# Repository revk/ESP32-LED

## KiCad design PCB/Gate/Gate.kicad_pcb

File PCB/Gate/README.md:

# Gate

## Trademark

This is an open source project, but bear in mind you cannot sell boards or cases bearing the Andrews & Arnold Ltd name, the A&A logo, the registered trademark AJK logo, or the GS1 allocated EANs assigned to Andrews & Arnold Ltd.

## PCB Designs

These files are for use with [KiCAD](https://www.kicad.org).

- [Gate](Gate.kicad_pro)

## 3D

3D case designs are normally automatically created from the PCB so as to ensure correct details and placement of apertures, etc.

- [Stargate](Stargate.stl)
- [StargateBottom](StargateBottom.stl)
- [StargateRamp](StargateRamp.stl)
- [StargateRampBottom](StargateRampBottom.stl)
- [StargateRampTop](StargateRampTop.stl)
- [StargateTop](StargateTop.stl)

## PCB Images

---

*Auto generated README.md 2025-11-09T11:03:06*

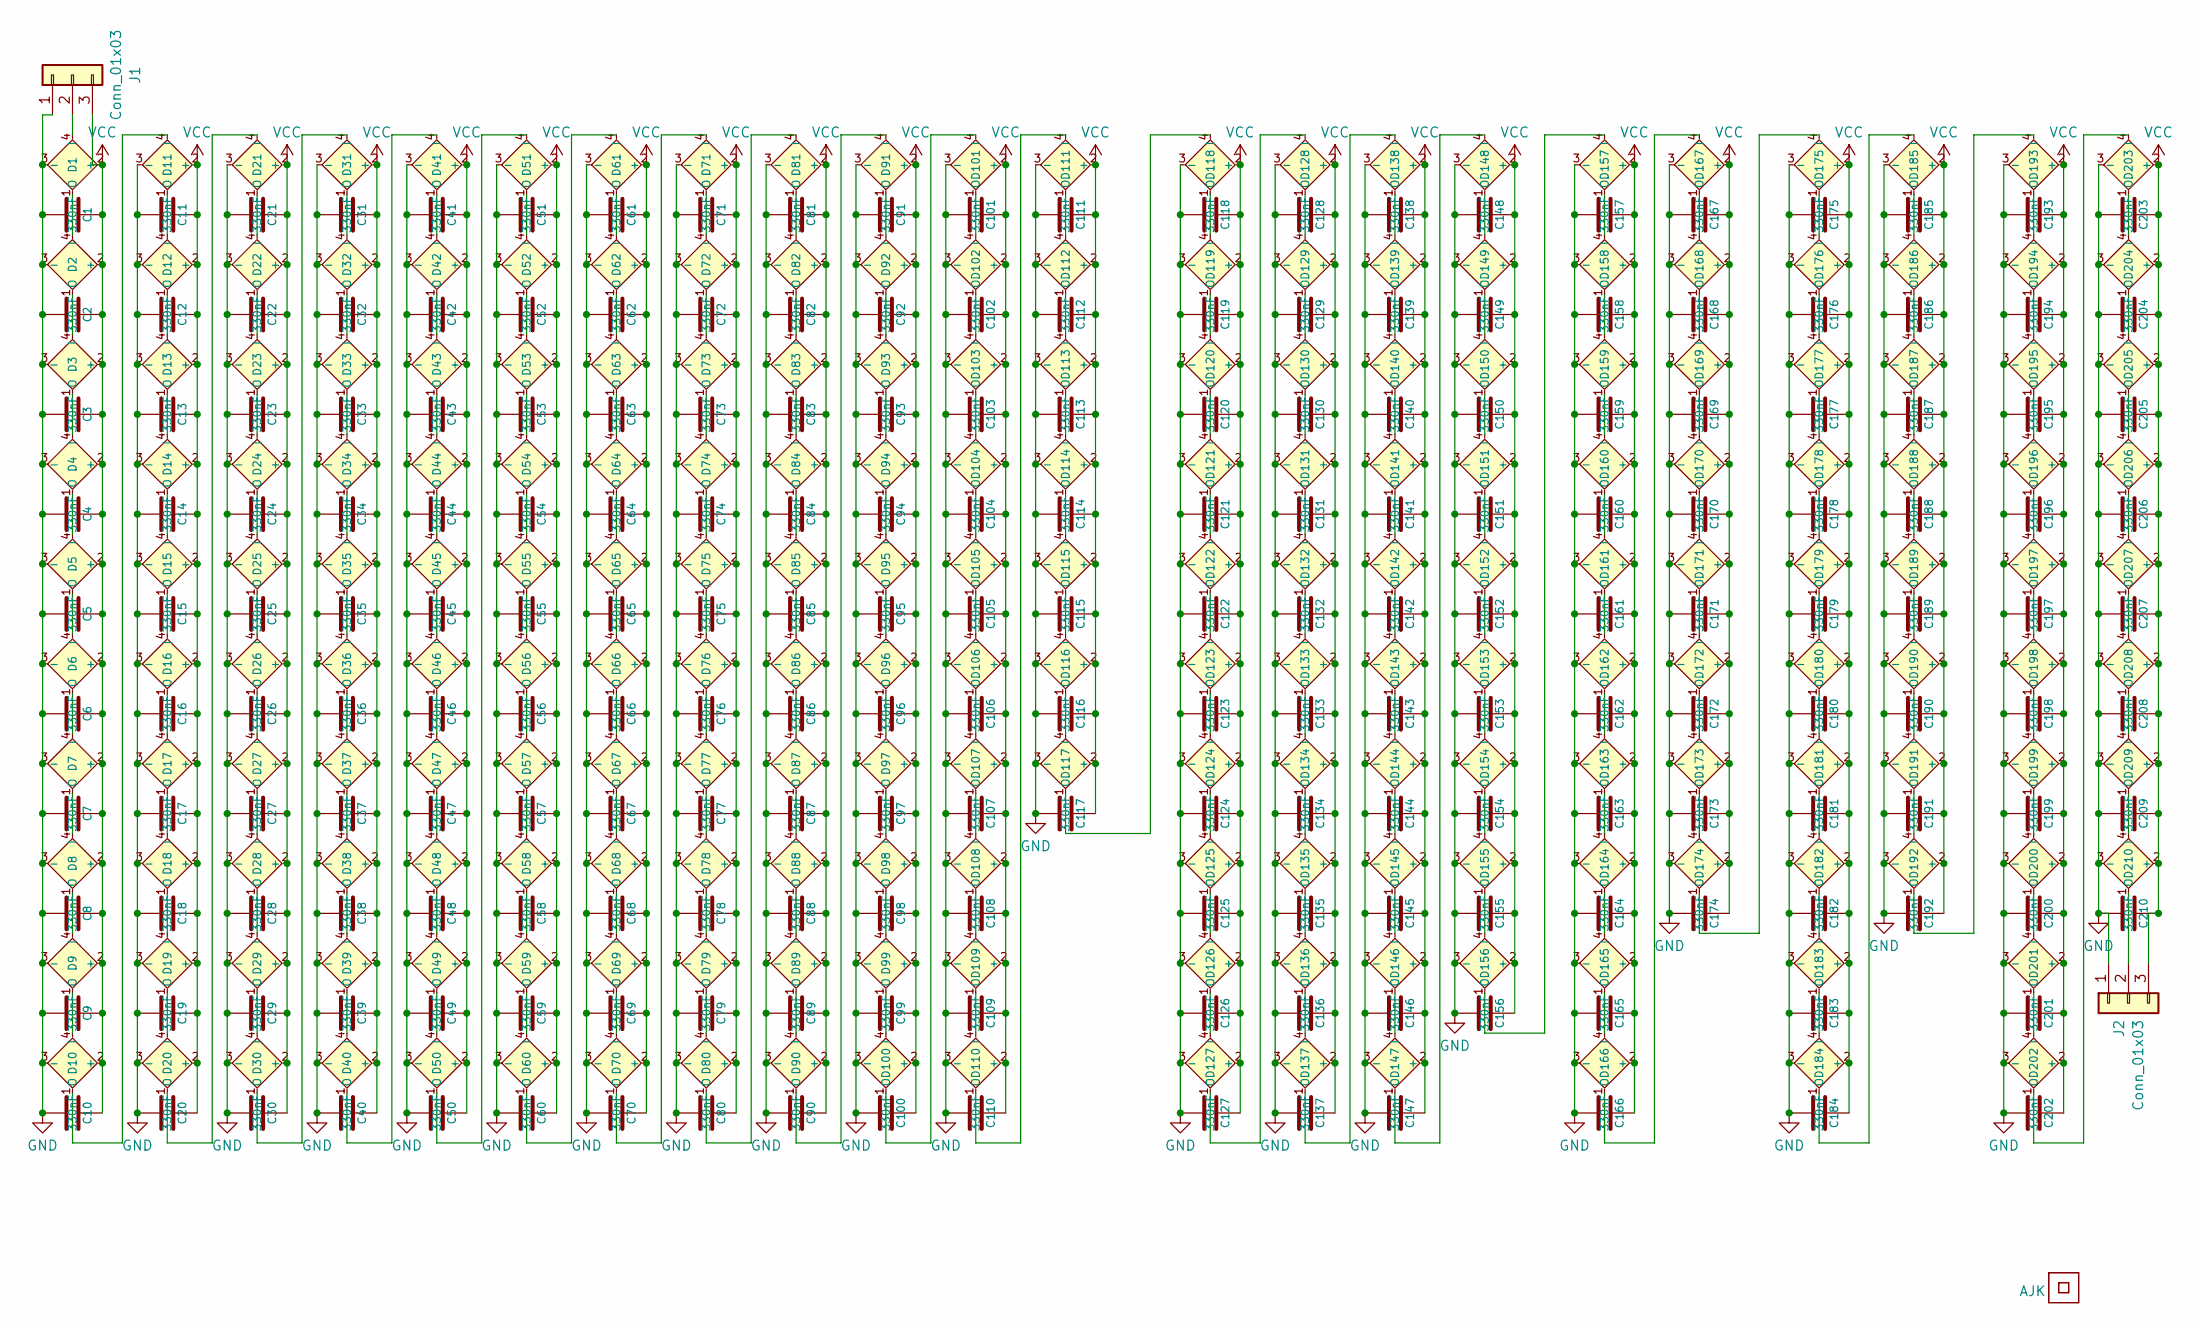
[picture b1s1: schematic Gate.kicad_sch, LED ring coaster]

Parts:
C1, C2, C3, C4, C5, C6, C7, C8, C9, C10, C11, C12, C13, C14, C15, C16, C17, C18, C19, C20, C21, C22, C23, C24, C25, C26, C27, C28, C29, C30, C31, C32, C33, C34, C35, C36, C37, C38, C39, C40, C41, C42, C43, C44, C45, C46, C47, C48, C49, C50, C51, C52, C53, C54, C55, C56, C57, C58, C59, C60, C61, C62, C63, C64, C65, C66, C67, C68, C69, C70, C71, C72, C73, C74, C75, C76, C77, C78, C79, C80, C81, C82, C83, C84, C85, C86, C87, C88, C89, C90, C91, C92, C93, C94, C95, C96, C97, C98, C99, C100, C101, C102, C103, C104, C105, C106, C107, C108, C109, C110, C111, C112, C113, C114, C115, C116, C117, C118, C119, C120, C121, C122, C123, C124, C125, C126, C127, C128, C129, C130, C131, C132, C133, C134, C135, C136, C137, C138, C139, C140, C141, C142, C143, C144, C145, C146, C147, C148, C149, C150, C151, C152, C153, C154, C155, C156, C157, C158, C159, C160, C161, C162, C163, C164, C165, C166, C167, C168, C169, C170, C171, C172, C173, C174, C175, C176, C177, C178, C179, C180, C181, C182, C183, C184, C185, C186, C187, C188, C189, C190, C191, C192, C193, C194, C195, C196, C197, C198, C199, C200, C201, C202, C203, C204, C205, C206, C207, C208, C209, C210: 330nF; C_0402
D1, D2, D3, D4, D5, D6, D7, D8, D9, D10, D11, D12, D13, D14, D15, D16, D17, D18, D19, D20, D21, D22, D23, D24, D25, D26, D27, D28, D29, D30, D31, D32, D33, D34, D35, D36, D37, D38, D39, D40, D41, D42, D43, D44, D45, D46, D47, D48, D49, D50, D51, D52, D53, D54, D55, D56, D57, D58, D59, D60, D61, D62, D63, D64, D65, D66, D67, D68, D69, D70, D71, D72, D73, D74, D75, D76, D77, D78, D79, D80, D81, D82, D83, D84, D85, D86, D87, D88, D89, D90, D91, D92, D93, D94, D95, D96, D97, D98, D99, D100, D101, D102, D103, D104, D105, D106, D107, D108, D109, D110, D111, D112, D113, D114, D115, D116, D117, D118, D119, D120, D121, D122, D123, D124, D125, D126, D127, D128, D129, D130, D131, D132, D133, D134, D135, D136, D137, D138, D139, D140, D141, D142, D143, D144, D145, D146, D147, D148, D149, D150, D151, D152, D153, D154, D155, D156, D157, D158, D159, D160, D161, D162, D163, D164, D165, D166, D167, D168, D169, D170, D171, D172, D173, D174, D175, D176, D177, D178, D179, D180, D181, D182, D183, D184, D185, D186, D187, D188, D189, D190, D191, D192, D193, D194, D195, D196, D197, D198, D199, D200, D201, D202, D203, D204, D205, D206, D207, D208, D209, D210: XL-1010RGBC-WS2812B; SMD1010; LCSC Part # C5349953
J1, J2: Conn_01x03; 3-PADS
Logo1: AJK
U1: QR; QR-LED

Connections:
GND: C1.2, C2.2, C3.2, C4.2, C5.2, C6.2, C7.2, C8.2, C9.2, C10.2, C11.2, C12.2, C13.2, C14.2, C15.2, C16.2, C17.2, C18.2, C19.2, C20.2, C21.2, C22.2, C23.2, C24.2, C25.2, C26.2, C27.2, C28.2, C29.2, C30.2, C31.2, C32.2, C33.2, C34.2, C35.2, C36.2, C37.2, C38.2, C39.2, C40.2, C41.2, C42.2, C43.2, C44.2, C45.2, C46.2, C47.2, C48.2, C49.2, C50.2, C51.2, C52.2, C53.2, C54.2, C55.2, C56.2, C57.2, C58.2, C59.2, C60.2, C61.2, C62.2, C63.2, C64.2, C65.2, C66.2, C67.2, C68.2, C69.2, C70.2, C71.2, C72.2, C73.2, C74.2, C75.2, C76.2, C77.2, C78.2, C79.2, C80.2, C81.2, C82.2, C83.2, C84.2, C85.2, C86.2, C87.2, C88.2, C89.2, C90.2, C91.2, C92.2, C93.2, C94.2, C95.2, C96.2, C97.2, C98.2, C99.2, C100.2, C101.2, C102.2, C103.2, C104.2, C105.2, C106.2, C107.2, C108.2, C109.2, C110.2, C111.2, C112.2, C113.2, C114.2, C115.2, C116.2, C117.2, C118.2, C119.2, C120.2, C121.2, C122.2, C123.2, C124.2, C125.2, C126.2, C127.2, C128.2, C129.2, C130.2, C131.2, C132.2, C133.2, C134.2, C135.2, C136.2, C137.2, C138.2, C139.2, C140.2, C141.2, C142.2, C143.2, C144.2, C145.2, C146.2, C147.2, C148.2, C149.2, C150.2, C151.2, C152.2, C153.2, C154.2, C155.2, C156.2, C157.2, C158.2, C159.2, C160.2, C161.2, C162.2, C163.2, C164.2, C165.2, C166.2, C167.2, C168.2, C169.2, C170.2, C171.2, C172.2, C173.2, C174.2, C175.2, C176.2, C177.2, C178.2, C179.2, C180.2, C181.2, C182.2, C183.2, C184.2, C185.2, C186.2, C187.2, C188.2, C189.2, C190.2, C191.2, C192.2, C193.2, C194.2, C195.2, C196.2, C197.2, C198.2, C199.2, C200.2, C201.2, C202.2, C203.2, C204.2, C205.2, C206.2, C207.2, C208.2, C209.2, C210.2, D1.3 (-), D2.3 (-), D3.3 (-), D4.3 (-), D5.3 (-), D6.3 (-), D7.3 (-), D8.3 (-), D9.3 (-), D10.3 (-), D11.3 (-), D12.3 (-), D13.3 (-), D14.3 (-), D15.3 (-), D16.3 (-), D17.3 (-), D18.3 (-), D19.3 (-), D20.3 (-), D21.3 (-), D22.3 (-), D23.3 (-), D24.3 (-), D25.3 (-), D26.3 (-), D27.3 (-), D28.3 (-), D29.3 (-), D30.3 (-), D31.3 (-), D32.3 (-), D33.3 (-), D34.3 (-), D35.3 (-), D36.3 (-), D37.3 (-), D38.3 (-), D39.3 (-), D40.3 (-), D41.3 (-), D42.3 (-), D43.3 (-), D44.3 (-), D45.3 (-), D46.3 (-), D47.3 (-), D48.3 (-), D49.3 (-), D50.3 (-), D51.3 (-), D52.3 (-), D53.3 (-), D54.3 (-), D55.3 (-), D56.3 (-), D57.3 (-), D58.3 (-), D59.3 (-), D60.3 (-), D61.3 (-), D62.3 (-), D63.3 (-), D64.3 (-), D65.3 (-), D66.3 (-), D67.3 (-), D68.3 (-), D69.3 (-), D70.3 (-), D71.3 (-), D72.3 (-), D73.3 (-), D74.3 (-), D75.3 (-), D76.3 (-), D77.3 (-), D78.3 (-), D79.3 (-), D80.3 (-), D81.3 (-), D82.3 (-), D83.3 (-), D84.3 (-), D85.3 (-), D86.3 (-), D87.3 (-), D88.3 (-), D89.3 (-), D90.3 (-), D91.3 (-), D92.3 (-), D93.3 (-), D94.3 (-), D95.3 (-), D96.3 (-), D97.3 (-), D98.3 (-), D99.3 (-), D100.3 (-), D101.3 (-), D102.3 (-), D103.3 (-), D104.3 (-), D105.3 (-), D106.3 (-), D107.3 (-), D108.3 (-), D109.3 (-), D110.3 (-), D111.3 (-), D112.3 (-), D113.3 (-), D114.3 (-), D115.3 (-), D116.3 (-), D117.3 (-), D118.3 (-), D119.3 (-), D120.3 (-), D121.3 (-), D122.3 (-), D123.3 (-), D124.3 (-), D125.3 (-), D126.3 (-), D127.3 (-), D128.3 (-), D129.3 (-), D130.3 (-), D131.3 (-), D132.3 (-), D133.3 (-), D134.3 (-), D135.3 (-), D136.3 (-), D137.3 (-), D138.3 (-), D139.3 (-), D140.3 (-), D141.3 (-), D142.3 (-), D143.3 (-), D144.3 (-), D145.3 (-), D146.3 (-), D147.3 (-), D148.3 (-), D149.3 (-), D150.3 (-), D151.3 (-), D152.3 (-), D153.3 (-), D154.3 (-), D155.3 (-), D156.3 (-), D157.3 (-), D158.3 (-), D159.3 (-), D160.3 (-), D161.3 (-), D162.3 (-), D163.3 (-), D164.3 (-), D165.3 (-), D166.3 (-), D167.3 (-), D168.3 (-), D169.3 (-), D170.3 (-), D171.3 (-), D172.3 (-), D173.3 (-), D174.3 (-), D175.3 (-), D176.3 (-), D177.3 (-), D178.3 (-), D179.3 (-), D180.3 (-), D181.3 (-), D182.3 (-), D183.3 (-), D184.3 (-), D185.3 (-), D186.3 (-), D187.3 (-), D188.3 (-), D189.3 (-), D190.3 (-), D191.3 (-), D192.3 (-), D193.3 (-), D194.3 (-), D195.3 (-), D196.3 (-), D197.3 (-), D198.3 (-), D199.3 (-), D200.3 (-), D201.3 (-), D202.3 (-), D203.3 (-), D204.3 (-), D205.3 (-), D206.3 (-), D207.3 (-), D208.3 (-), D209.3 (-), D210.3 (-), J1.1, J2.1
unnamed: D1.4 (I), J1.2
unnamed: D1.1 (O), D2.4 (I)
unnamed: D2.1 (O), D3.4 (I)
unnamed: D3.1 (O), D4.4 (I)
unnamed: D4.1 (O), D5.4 (I)
unnamed: D5.1 (O), D6.4 (I)
unnamed: D6.1 (O), D7.4 (I)
unnamed: D7.1 (O), D8.4 (I)
unnamed: D8.1 (O), D9.4 (I)
unnamed: D9.1 (O), D10.4 (I)
unnamed: D10.1 (O), D11.4 (I)
unnamed: D11.1 (O), D12.4 (I)
unnamed: D12.1 (O), D13.4 (I)
unnamed: D13.1 (O), D14.4 (I)
unnamed: D14.1 (O), D15.4 (I)
unnamed: D15.1 (O), D16.4 (I)
unnamed: D16.1 (O), D17.4 (I)
unnamed: D17.1 (O), D18.4 (I)
unnamed: D18.1 (O), D19.4 (I)
unnamed: D19.1 (O), D20.4 (I)
unnamed: D20.1 (O), D21.4 (I)
unnamed: D21.1 (O), D22.4 (I)
unnamed: D22.1 (O), D23.4 (I)
unnamed: D23.1 (O), D24.4 (I)
unnamed: D24.1 (O), D25.4 (I)
unnamed: D25.1 (O), D26.4 (I)
unnamed: D26.1 (O), D27.4 (I)
unnamed: D27.1 (O), D28.4 (I)
unnamed: D28.1 (O), D29.4 (I)
unnamed: D29.1 (O), D30.4 (I)
unnamed: D30.1 (O), D31.4 (I)
unnamed: D31.1 (O), D32.4 (I)
unnamed: D32.1 (O), D33.4 (I)
unnamed: D33.1 (O), D34.4 (I)
unnamed: D34.1 (O), D35.4 (I)
unnamed: D35.1 (O), D36.4 (I)
unnamed: D36.1 (O), D37.4 (I)
unnamed: D37.1 (O), D38.4 (I)
unnamed: D38.1 (O), D39.4 (I)
unnamed: D39.1 (O), D40.4 (I)
unnamed: D40.1 (O), D41.4 (I)
unnamed: D41.1 (O), D42.4 (I)
unnamed: D42.1 (O), D43.4 (I)
unnamed: D43.1 (O), D44.4 (I)
unnamed: D44.1 (O), D45.4 (I)
unnamed: D45.1 (O), D46.4 (I)
unnamed: D46.1 (O), D47.4 (I)
unnamed: D47.1 (O), D48.4 (I)
unnamed: D48.1 (O), D49.4 (I)
unnamed: D49.1 (O), D50.4 (I)
unnamed: D50.1 (O), D51.4 (I)
unnamed: D51.1 (O), D52.4 (I)
unnamed: D52.1 (O), D53.4 (I)
unnamed: D53.1 (O), D54.4 (I)
unnamed: D54.1 (O), D55.4 (I)
unnamed: D55.1 (O), D56.4 (I)
unnamed: D56.1 (O), D57.4 (I)
unnamed: D57.1 (O), D58.4 (I)
unnamed: D58.1 (O), D59.4 (I)
unnamed: D59.1 (O), D60.4 (I)
unnamed: D60.1 (O), D61.4 (I)
unnamed: D61.1 (O), D62.4 (I)
unnamed: D62.1 (O), D63.4 (I)
unnamed: D63.1 (O), D64.4 (I)
unnamed: D64.1 (O), D65.4 (I)
unnamed: D65.1 (O), D66.4 (I)
unnamed: D66.1 (O), D67.4 (I)
unnamed: D67.1 (O), D68.4 (I)
unnamed: D68.1 (O), D69.4 (I)
unnamed: D69.1 (O), D70.4 (I)
unnamed: D70.1 (O), D71.4 (I)
unnamed: D71.1 (O), D72.4 (I)
unnamed: D72.1 (O), D73.4 (I)
unnamed: D73.1 (O), D74.4 (I)
unnamed: D74.1 (O), D75.4 (I)
unnamed: D75.1 (O), D76.4 (I)
unnamed: D76.1 (O), D77.4 (I)
unnamed: D77.1 (O), D78.4 (I)
unnamed: D78.1 (O), D79.4 (I)
unnamed: D79.1 (O), D80.4 (I)
unnamed: D80.1 (O), D81.4 (I)
unnamed: D81.1 (O), D82.4 (I)
unnamed: D82.1 (O), D83.4 (I)
unnamed: D83.1 (O), D84.4 (I)
unnamed: D84.1 (O), D85.4 (I)
unnamed: D85.1 (O), D86.4 (I)
unnamed: D86.1 (O), D87.4 (I)
unnamed: D87.1 (O), D88.4 (I)
unnamed: D88.1 (O), D89.4 (I)
unnamed: D89.1 (O), D90.4 (I)
unnamed: D90.1 (O), D91.4 (I)
unnamed: D91.1 (O), D92.4 (I)
unnamed: D92.1 (O), D93.4 (I)
unnamed: D93.1 (O), D94.4 (I)
unnamed: D94.1 (O), D95.4 (I)
unnamed: D95.1 (O), D96.4 (I)
unnamed: D96.1 (O), D97.4 (I)
unnamed: D97.1 (O), D98.4 (I)
unnamed: D98.1 (O), D99.4 (I)
unnamed: D99.1 (O), D100.4 (I)
unnamed: D100.1 (O), D101.4 (I)
unnamed: D101.1 (O), D102.4 (I)
unnamed: D102.1 (O), D103.4 (I)
unnamed: D103.1 (O), D104.4 (I)
unnamed: D104.1 (O), D105.4 (I)
unnamed: D105.1 (O), D106.4 (I)
unnamed: D106.1 (O), D107.4 (I)
unnamed: D107.1 (O), D108.4 (I)
unnamed: D108.1 (O), D109.4 (I)
unnamed: D109.1 (O), D110.4 (I)
unnamed: D110.1 (O), D111.4 (I)
unnamed: D111.1 (O), D112.4 (I)
unnamed: D112.1 (O), D113.4 (I)
unnamed: D113.1 (O), D114.4 (I)
unnamed: D114.1 (O), D115.4 (I)
unnamed: D115.1 (O), D116.4 (I)
unnamed: D116.1 (O), D117.4 (I)
unnamed: D117.1 (O), D118.4 (I)
unnamed: D118.1 (O), D119.4 (I)
unnamed: D119.1 (O), D120.4 (I)
unnamed: D120.1 (O), D121.4 (I)
unnamed: D121.1 (O), D122.4 (I)
unnamed: D122.1 (O), D123.4 (I)
unnamed: D123.1 (O), D124.4 (I)
unnamed: D124.1 (O), D125.4 (I)
unnamed: D125.1 (O), D126.4 (I)
unnamed: D126.1 (O), D127.4 (I)
unnamed: D127.1 (O), D128.4 (I)
unnamed: D128.1 (O), D129.4 (I)
unnamed: D129.1 (O), D130.4 (I)
unnamed: D130.1 (O), D131.4 (I)
unnamed: D131.1 (O), D132.4 (I)
unnamed: D132.1 (O), D133.4 (I)
unnamed: D133.1 (O), D134.4 (I)
unnamed: D134.1 (O), D135.4 (I)
unnamed: D135.1 (O), D136.4 (I)
unnamed: D136.1 (O), D137.4 (I)
unnamed: D137.1 (O), D138.4 (I)
unnamed: D138.1 (O), D139.4 (I)
unnamed: D139.1 (O), D140.4 (I)
unnamed: D140.1 (O), D141.4 (I)
unnamed: D141.1 (O), D142.4 (I)
unnamed: D142.1 (O), D143.4 (I)
unnamed: D143.1 (O), D144.4 (I)
unnamed: D144.1 (O), D145.4 (I)
unnamed: D145.1 (O), D146.4 (I)
unnamed: D146.1 (O), D147.4 (I)
unnamed: D147.1 (O), D148.4 (I)
unnamed: D148.1 (O), D149.4 (I)
unnamed: D149.1 (O), D150.4 (I)
unnamed: D150.1 (O), D151.4 (I)
unnamed: D151.1 (O), D152.4 (I)
unnamed: D152.1 (O), D153.4 (I)
unnamed: D153.1 (O), D154.4 (I)
unnamed: D154.1 (O), D155.4 (I)
unnamed: D155.1 (O), D156.4 (I)
unnamed: D156.1 (O), D157.4 (I)
unnamed: D157.1 (O), D158.4 (I)
unnamed: D158.1 (O), D159.4 (I)
unnamed: D159.1 (O), D160.4 (I)
unnamed: D160.1 (O), D161.4 (I)
unnamed: D161.1 (O), D162.4 (I)
unnamed: D162.1 (O), D163.4 (I)
unnamed: D163.1 (O), D164.4 (I)
unnamed: D164.1 (O), D165.4 (I)
unnamed: D165.1 (O), D166.4 (I)
unnamed: D166.1 (O), D167.4 (I)
unnamed: D167.1 (O), D168.4 (I)
unnamed: D168.1 (O), D169.4 (I)
unnamed: D169.1 (O), D170.4 (I)
unnamed: D170.1 (O), D171.4 (I)
unnamed: D171.1 (O), D172.4 (I)
unnamed: D172.1 (O), D173.4 (I)
unnamed: D173.1 (O), D174.4 (I)
unnamed: D174.1 (O), D175.4 (I)
unnamed: D175.1 (O), D176.4 (I)
unnamed: D176.1 (O), D177.4 (I)
unnamed: D177.1 (O), D178.4 (I)
unnamed: D178.1 (O), D179.4 (I)
unnamed: D179.1 (O), D180.4 (I)
unnamed: D180.1 (O), D181.4 (I)
unnamed: D181.1 (O), D182.4 (I)
unnamed: D182.1 (O), D183.4 (I)
unnamed: D183.1 (O), D184.4 (I)
unnamed: D184.1 (O), D185.4 (I)
unnamed: D185.1 (O), D186.4 (I)
unnamed: D186.1 (O), D187.4 (I)
unnamed: D187.1 (O), D188.4 (I)
unnamed: D188.1 (O), D189.4 (I)
unnamed: D189.1 (O), D190.4 (I)
unnamed: D190.1 (O), D191.4 (I)
unnamed: D191.1 (O), D192.4 (I)
unnamed: D192.1 (O), D193.4 (I)
unnamed: D193.1 (O), D194.4 (I)
unnamed: D194.1 (O), D195.4 (I)
unnamed: D195.1 (O), D196.4 (I)
unnamed: D196.1 (O), D197.4 (I)
unnamed: D197.1 (O), D198.4 (I)
unnamed: D198.1 (O), D199.4 (I)
unnamed: D199.1 (O), D200.4 (I)
unnamed: D200.1 (O), D201.4 (I)
unnamed: D201.1 (O), D202.4 (I)
unnamed: D202.1 (O), D203.4 (I)
unnamed: D203.1 (O), D204.4 (I)
unnamed: D204.1 (O), D205.4 (I)
unnamed: D205.1 (O), D206.4 (I)
unnamed: D206.1 (O), D207.4 (I)
unnamed: D207.1 (O), D208.4 (I)
unnamed: D208.1 (O), D209.4 (I)
unnamed: D209.1 (O), D210.4 (I)
unnamed: D210.1 (O), J2.2
VCC: C1.1, C2.1, C3.1, C4.1, C5.1, C6.1, C7.1, C8.1, C9.1, C10.1, C11.1, C12.1, C13.1, C14.1, C15.1, C16.1, C17.1, C18.1, C19.1, C20.1, C21.1, C22.1, C23.1, C24.1, C25.1, C26.1, C27.1, C28.1, C29.1, C30.1, C31.1, C32.1, C33.1, C34.1, C35.1, C36.1, C37.1, C38.1, C39.1, C40.1, C41.1, C42.1, C43.1, C44.1, C45.1, C46.1, C47.1, C48.1, C49.1, C50.1, C51.1, C52.1, C53.1, C54.1, C55.1, C56.1, C57.1, C58.1, C59.1, C60.1, C61.1, C62.1, C63.1, C64.1, C65.1, C66.1, C67.1, C68.1, C69.1, C70.1, C71.1, C72.1, C73.1, C74.1, C75.1, C76.1, C77.1, C78.1, C79.1, C80.1, C81.1, C82.1, C83.1, C84.1, C85.1, C86.1, C87.1, C88.1, C89.1, C90.1, C91.1, C92.1, C93.1, C94.1, C95.1, C96.1, C97.1, C98.1, C99.1, C100.1, C101.1, C102.1, C103.1, C104.1, C105.1, C106.1, C107.1, C108.1, C109.1, C110.1, C111.1, C112.1, C113.1, C114.1, C115.1, C116.1, C117.1, C118.1, C119.1, C120.1, C121.1, C122.1, C123.1, C124.1, C125.1, C126.1, C127.1, C128.1, C129.1, C130.1, C131.1, C132.1, C133.1, C134.1, C135.1, C136.1, C137.1, C138.1, C139.1, C140.1, C141.1, C142.1, C143.1, C144.1, C145.1, C146.1, C147.1, C148.1, C149.1, C150.1, C151.1, C152.1, C153.1, C154.1, C155.1, C156.1, C157.1, C158.1, C159.1, C160.1, C161.1, C162.1, C163.1, C164.1, C165.1, C166.1, C167.1, C168.1, C169.1, C170.1, C171.1, C172.1, C173.1, C174.1, C175.1, C176.1, C177.1, C178.1, C179.1, C180.1, C181.1, C182.1, C183.1, C184.1, C185.1, C186.1, C187.1, C188.1, C189.1, C190.1, C191.1, C192.1, C193.1, C194.1, C195.1, C196.1, C197.1, C198.1, C199.1, C200.1, C201.1, C202.1, C203.1, C204.1, C205.1, C206.1, C207.1, C208.1, C209.1, C210.1, D1.2 (+), D2.2 (+), D3.2 (+), D4.2 (+), D5.2 (+), D6.2 (+), D7.2 (+), D8.2 (+), D9.2 (+), D10.2 (+), D11.2 (+), D12.2 (+), D13.2 (+), D14.2 (+), D15.2 (+), D16.2 (+), D17.2 (+), D18.2 (+), D19.2 (+), D20.2 (+), D21.2 (+), D22.2 (+), D23.2 (+), D24.2 (+), D25.2 (+), D26.2 (+), D27.2 (+), D28.2 (+), D29.2 (+), D30.2 (+), D31.2 (+), D32.2 (+), D33.2 (+), D34.2 (+), D35.2 (+), D36.2 (+), D37.2 (+), D38.2 (+), D39.2 (+), D40.2 (+), D41.2 (+), D42.2 (+), D43.2 (+), D44.2 (+), D45.2 (+), D46.2 (+), D47.2 (+), D48.2 (+), D49.2 (+), D50.2 (+), D51.2 (+), D52.2 (+), D53.2 (+), D54.2 (+), D55.2 (+), D56.2 (+), D57.2 (+), D58.2 (+), D59.2 (+), D60.2 (+), D61.2 (+), D62.2 (+), D63.2 (+), D64.2 (+), D65.2 (+), D66.2 (+), D67.2 (+), D68.2 (+), D69.2 (+), D70.2 (+), D71.2 (+), D72.2 (+), D73.2 (+), D74.2 (+), D75.2 (+), D76.2 (+), D77.2 (+), D78.2 (+), D79.2 (+), D80.2 (+), D81.2 (+), D82.2 (+), D83.2 (+), D84.2 (+), D85.2 (+), D86.2 (+), D87.2 (+), D88.2 (+), D89.2 (+), D90.2 (+), D91.2 (+), D92.2 (+), D93.2 (+), D94.2 (+), D95.2 (+), D96.2 (+), D97.2 (+), D98.2 (+), D99.2 (+), D100.2 (+), D101.2 (+), D102.2 (+), D103.2 (+), D104.2 (+), D105.2 (+), D106.2 (+), D107.2 (+), D108.2 (+), D109.2 (+), D110.2 (+), D111.2 (+), D112.2 (+), D113.2 (+), D114.2 (+), D115.2 (+), D116.2 (+), D117.2 (+), D118.2 (+), D119.2 (+), D120.2 (+), D121.2 (+), D122.2 (+), D123.2 (+), D124.2 (+), D125.2 (+), D126.2 (+), D127.2 (+), D128.2 (+), D129.2 (+), D130.2 (+), D131.2 (+), D132.2 (+), D133.2 (+), D134.2 (+), D135.2 (+), D136.2 (+), D137.2 (+), D138.2 (+), D139.2 (+), D140.2 (+), D141.2 (+), D142.2 (+), D143.2 (+), D144.2 (+), D145.2 (+), D146.2 (+), D147.2 (+), D148.2 (+), D149.2 (+), D150.2 (+), D151.2 (+), D152.2 (+), D153.2 (+), D154.2 (+), D155.2 (+), D156.2 (+), D157.2 (+), D158.2 (+), D159.2 (+), D160.2 (+), D161.2 (+), D162.2 (+), D163.2 (+), D164.2 (+), D165.2 (+), D166.2 (+), D167.2 (+), D168.2 (+), D169.2 (+), D170.2 (+), D171.2 (+), D172.2 (+), D173.2 (+), D174.2 (+), D175.2 (+), D176.2 (+), D177.2 (+), D178.2 (+), D179.2 (+), D180.2 (+), D181.2 (+), D182.2 (+), D183.2 (+), D184.2 (+), D185.2 (+), D186.2 (+), D187.2 (+), D188.2 (+), D189.2 (+), D190.2 (+), D191.2 (+), D192.2 (+), D193.2 (+), D194.2 (+), D195.2 (+), D196.2 (+), D197.2 (+), D198.2 (+), D199.2 (+), D200.2 (+), D201.2 (+), D202.2 (+), D203.2 (+), D204.2 (+), D205.2 (+), D206.2 (+), D207.2 (+), D208.2 (+), D209.2 (+), D210.2 (+), J1.3, J2.3

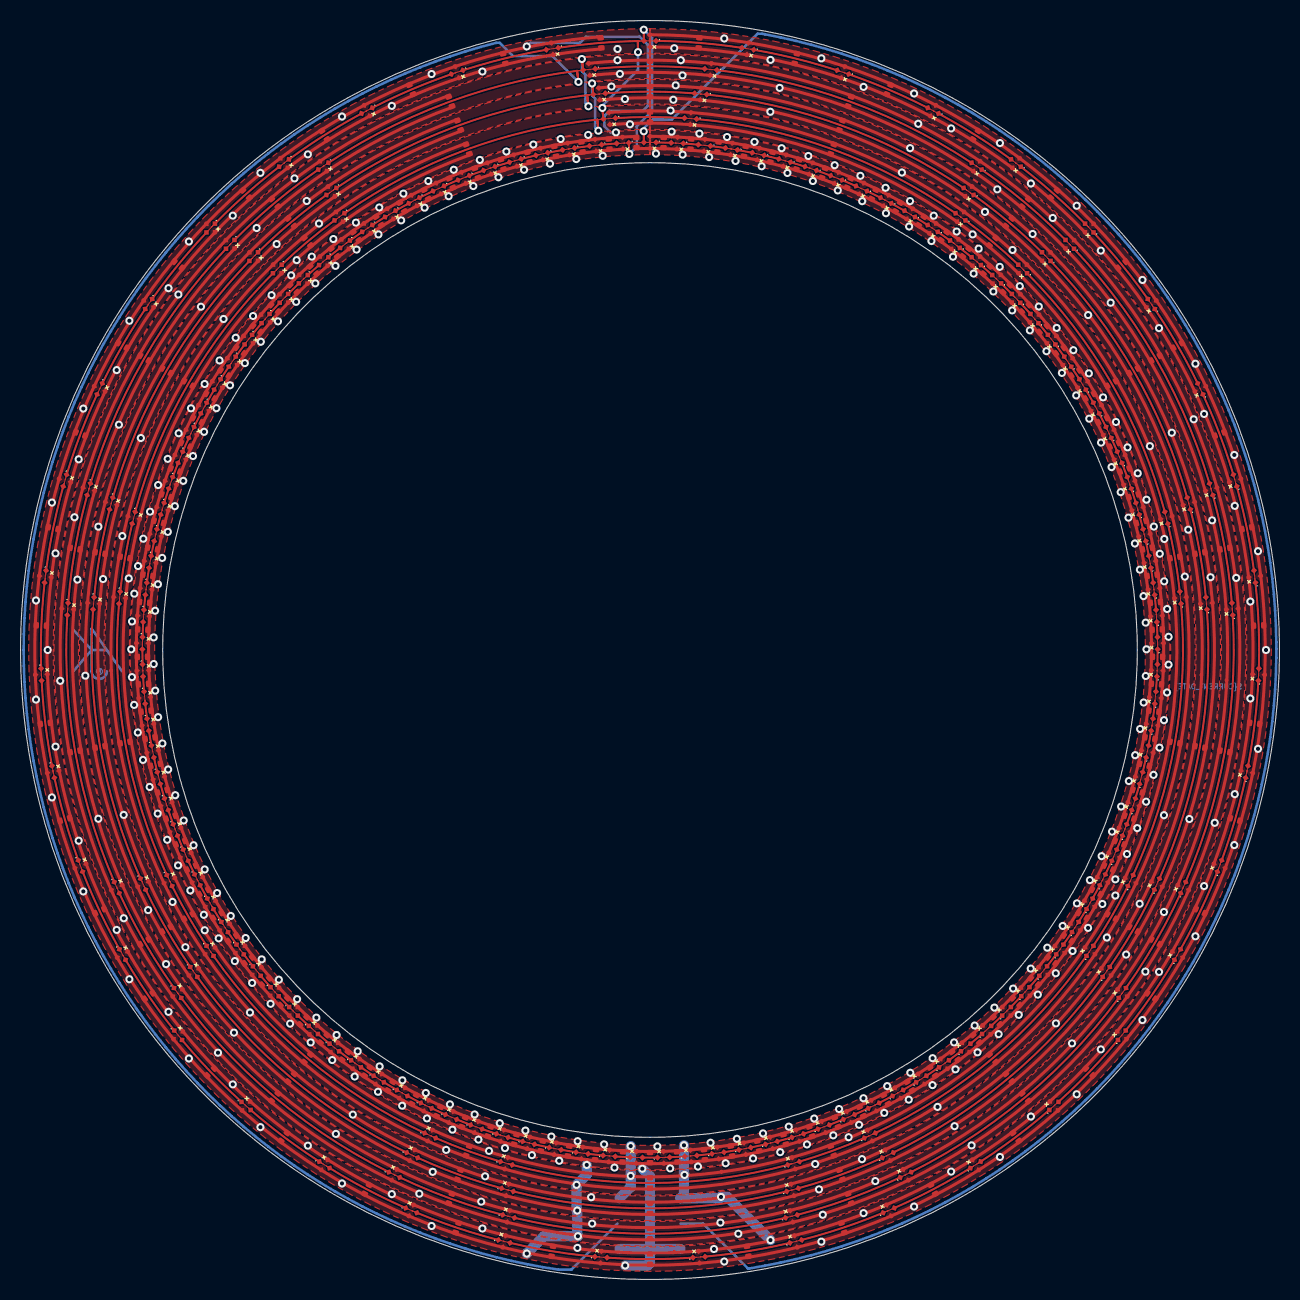
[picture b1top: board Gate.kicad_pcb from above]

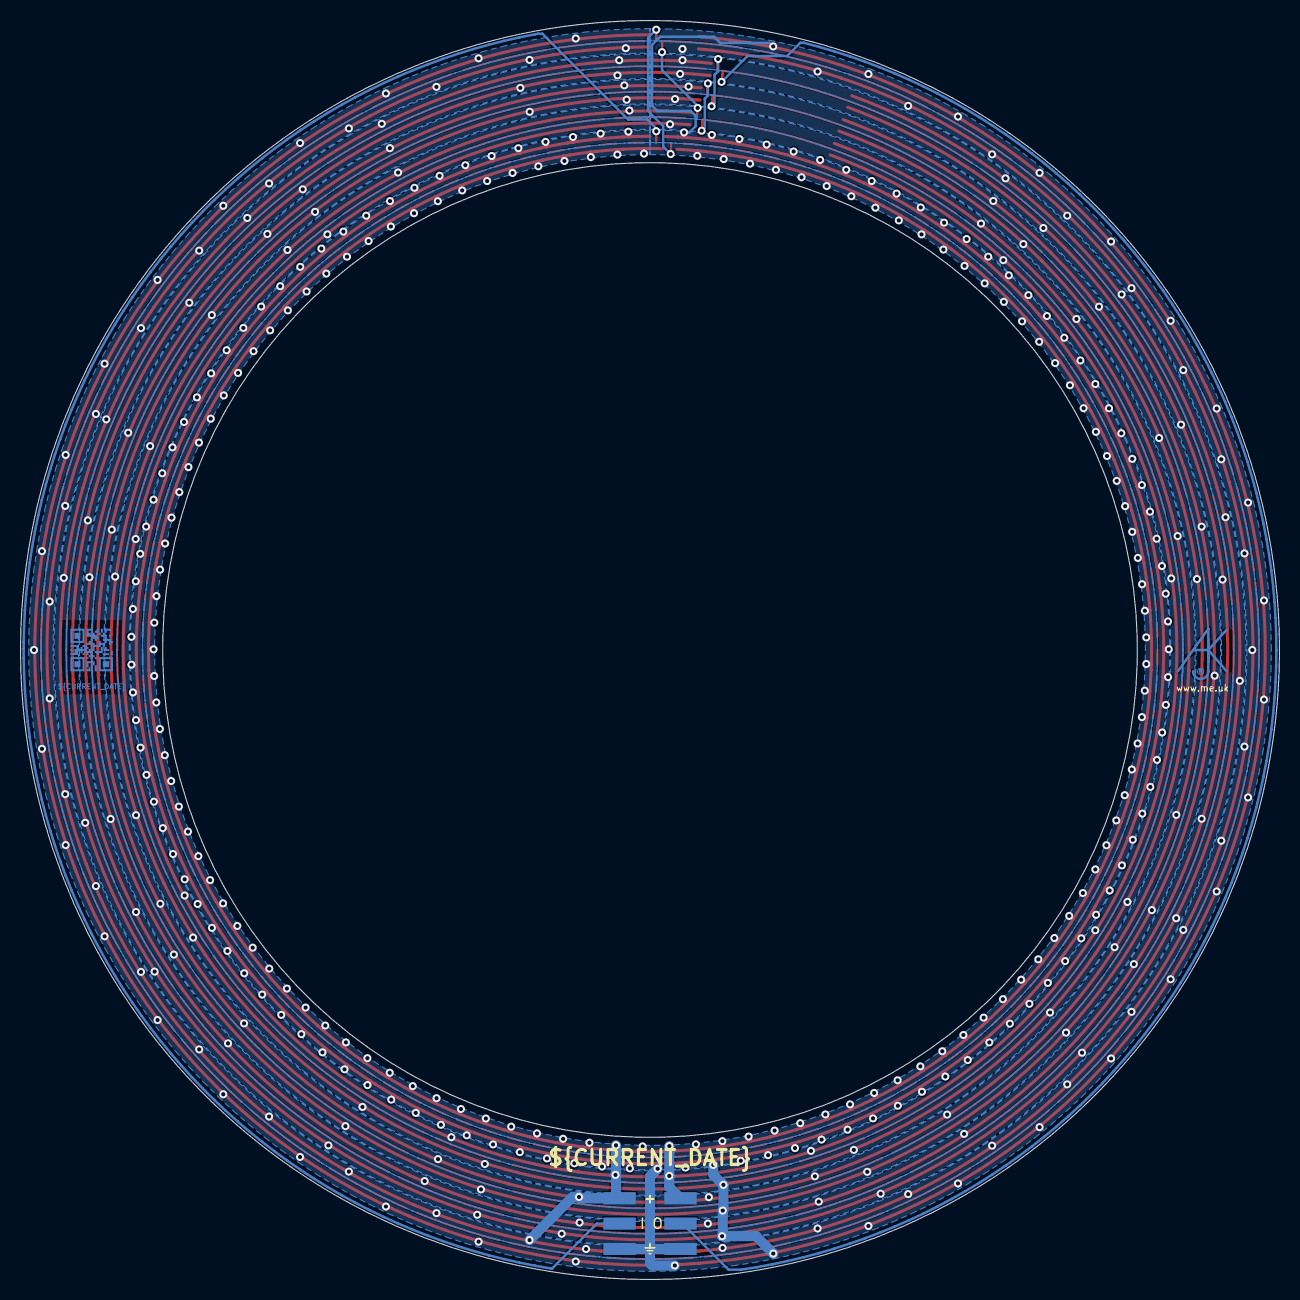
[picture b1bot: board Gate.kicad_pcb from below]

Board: 2 copper layers, 124.0 x 124.0 mm, 424 parts (4 on the bottom side), 213 nets.

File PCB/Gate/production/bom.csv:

Designator,Footprint,Quantity,Value,LCSC Part #
"C1, C10, C100, C101, C102, C103, C104, C105, C106, C107, C108, C109, C11, C110, C111, C112, C113, C114, C115, C116, C117, C118, C119, C12, C120, C121, C122, C123, C124, C125, C126, C127, C128, C129, C13, C130, C131, C132, C133, C134, C135, C136, C137, C138, C139, C14, C140, C141, C142, C143, C144, C145, C146, C147, C148, C149, C15, C150, C151, C152, C153, C154, C155, C156, C157, C158, C159, C16, C160, C161, C162, C163, C164, C165, C166, C167, C168, C169, C17, C170, C171, C172, C173, C174, C175, C176, C177, C178, C179, C18, C180, C181, C182, C183, C184, C185, C186, C187, C188, C189, C19, C190, C191, C192, C193, C194, C195, C196, C197, C198, C199, C2, C20, C200, C201, C202, C203, C204, C205, C206, C207, C208, C209, C21, C210, C22, C23, C24, C25, C26, C27, C28, C29, C3, C30, C31, C32, C33, C34, C35, C36, C37, C38, C39, C4, C40, C41, C42, C43, C44, C45, C46, C47, C48, C49, C5, C50, C51, C52, C53, C54, C55, C56, C57, C58, C59, C6, C60, C61, C62, C63, C64, C65, C66, C67, C68, C69, C7, C70, C71, C72, C73, C74, C75, C76, C77, C78, C79, C8, C80, C81, C82, C83, C84, C85, C86, C87, C88, C89, C9, C90, C91, C92, C93, C94, C95, C96, C97, C98, C99",C_0402,210,330nF,
"D1, D10, D100, D101, D102, D103, D104, D105, D106, D107, D108, D109, D11, D110, D111, D112, D113, D114, D115, D116, D117, D118, D119, D12, D120, D121, D122, D123, D124, D125, D126, D127, D128, D129, D13, D130, D131, D132, D133, D134, D135, D136, D137, D138, D139, D14, D140, D141, D142, D143, D144, D145, D146, D147, D148, D149, D15, D150, D151, D152, D153, D154, D155, D156, D157, D158, D159, D16, D160, D161, D162, D163, D164, D165, D166, D167, D168, D169, D17, D170, D171, D172, D173, D174, D175, D176, D177, D178, D179, D18, D180, D181, D182, D183, D184, D185, D186, D187, D188, D189, D19, D190, D191, D192, D193, D194, D195, D196, D197, D198, D199, D2, D20, D200, D201, D202, D203, D204, D205, D206, D207, D208, D209, D21, D210, D22, D23, D24, D25, D26, D27, D28, D29, D3, D30, D31, D32, D33, D34, D35, D36, D37, D38, D39, D4, D40, D41, D42, D43, D44, D45, D46, D47, D48, D49, D5, D50, D51, D52, D53, D54, D55, D56, D57, D58, D59, D6, D60, D61, D62, D63, D64, D65, D66, D67, D68, D69, D7, D70, D71, D72, D73, D74, D75, D76, D77, D78, D79, D8, D80, D81, D82, D83, D84, D85, D86, D87, D88, D89, D9, D90, D91, D92, D93, D94, D95, D96, D97, D98, D99",SMD1010,210,XL-1010RGBC-WS2812B,C5349953
"J1, J2",3-PADS,2,Conn_01x03,

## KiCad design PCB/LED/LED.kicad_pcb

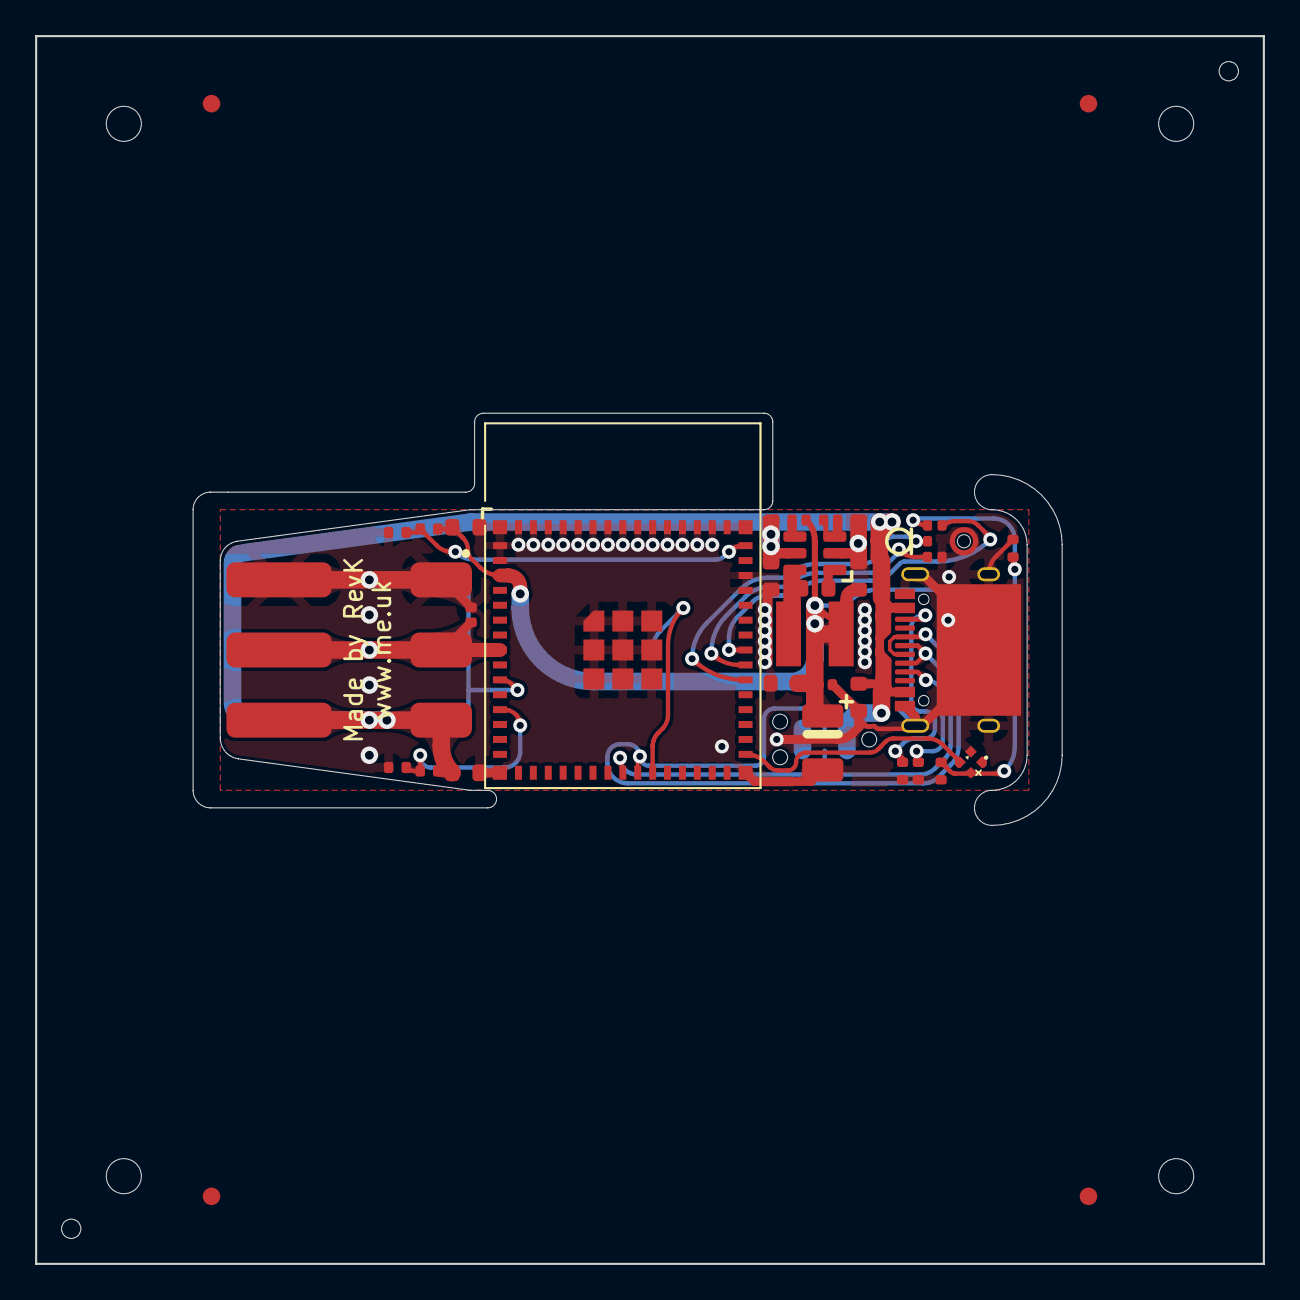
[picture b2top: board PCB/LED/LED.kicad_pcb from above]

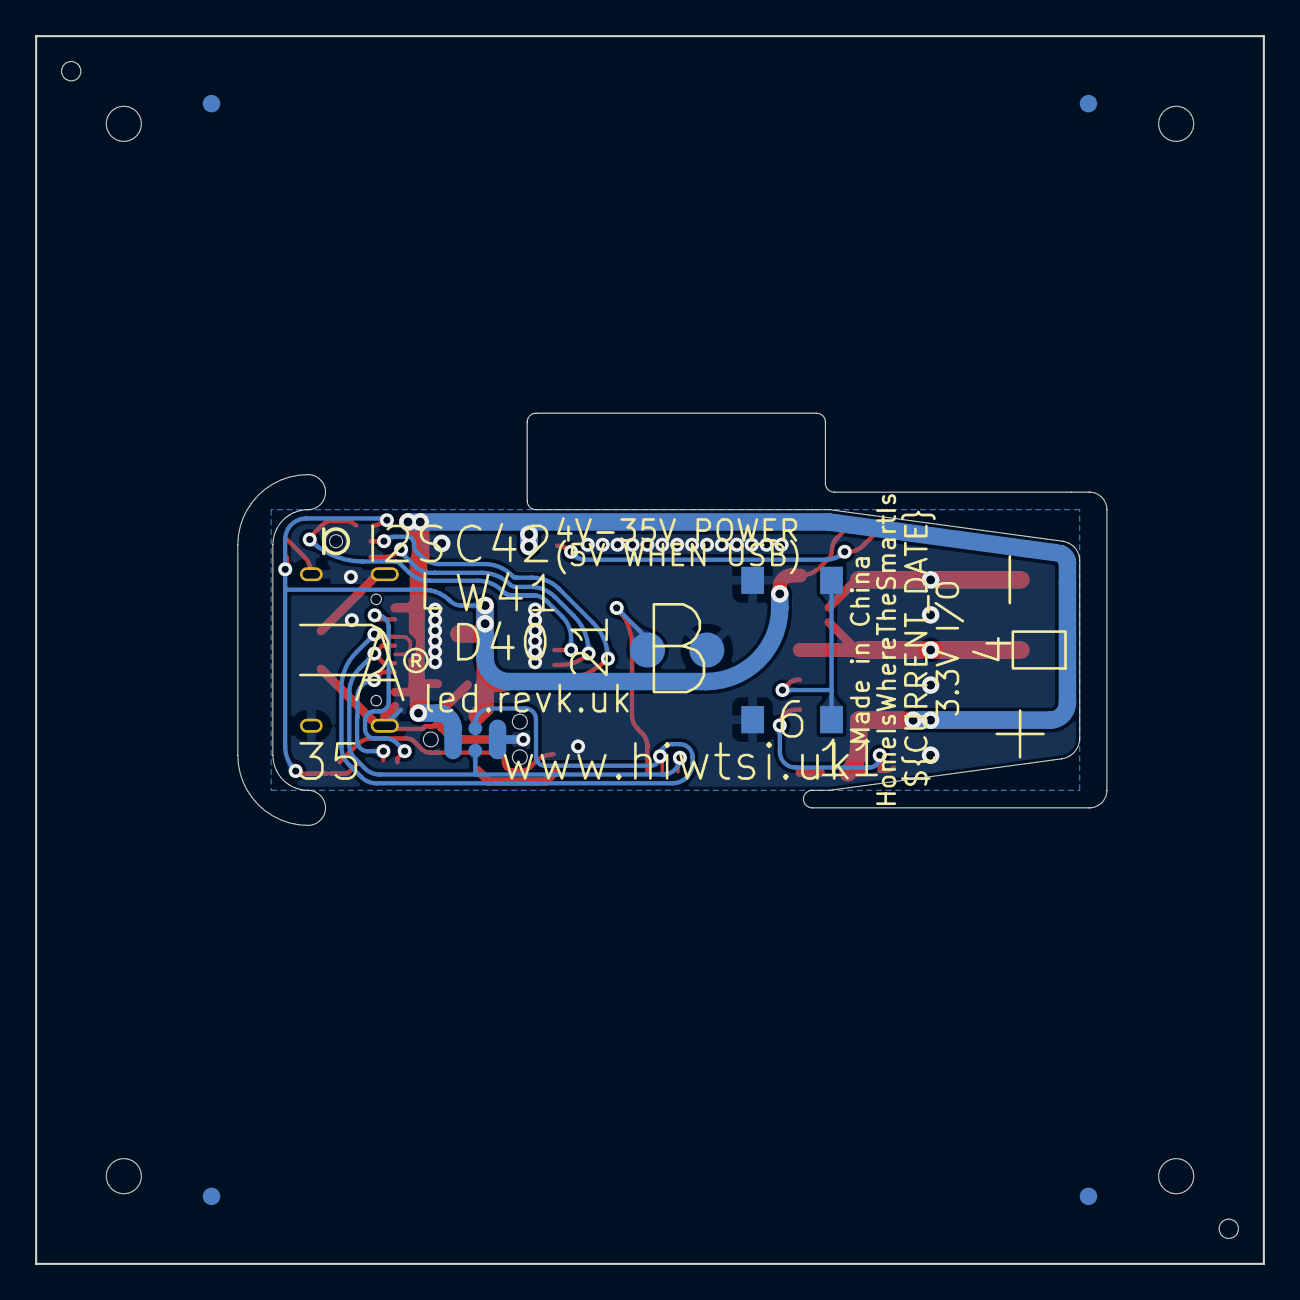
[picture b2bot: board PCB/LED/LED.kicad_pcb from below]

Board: 2 copper layers, 70.0 x 70.0 mm, 34 parts (3 on the bottom side), 16 nets.

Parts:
C1: 220uF Tant; CP_EIA-3528-21_Kemet-B
C2, C4, C8: 100nF; C_0402
C3: 22uF; C_0603
C5, C6, C7: 10uF 35V; C_0603
C9: 1uF; C_0402
C10: 10uF 35V; C_0603_
C11: 10uF 6.3V; C_0603_
C12: 100nF; C_0603_
D1: XL-1010RGBC-WS2812B; SMD1010
D2: DFN1006-2L
J1: Reset; AA-Pad
J2: Wago; WAGO-2060-453-998-404
J3: TC2030-USB-NL-DS; Tag-Connect_TC2030-IDC-NL_2x03_P1.27mm_Vertical
J5: USB-C-Socket-H
L2: 10uH; L_4x4_
PCB1: 70x70; PCB7070
R1: 124K; R_0402
R2, R3: 10K; R_0402
R4: 124k; R_0402_
R5, R6: 5K1; R_0402
R14: 39k2; R_0402_
R15: 1M; R_0402_
SW1: Button; SW_Push_1P1T_NO_6x6mm
U1: ICS43434_MEMS_Mic
U6: ESP32-S3-MINI-1
U7: MD8942; SOT-23-6-MD8942
V1, V2: VCUT70N

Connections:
+3V3: C1.1, C2.1, C3.1, C4.1, C7.1, C8.2, D1.2 (+), R2.1, U1.5 (VDD), U6.3 (3V3), U7.8 (VOUT)
ADC: R1.2, R3.1, U6.12 (GPIO8)
BLINK: D1.4 (I), U6.31 (GPIO35)
D+: J3.4 (D+), J5.A6 (D+), J5.B6 (D+), U6.24 (GPIO20)
D-: J3.3 (D-), J5.A7 (D-), J5.B7 (D-), U6.23 (GPIO19)
DC: C5.1, C6.1, J2.3, J3.1 (VBUS), J3.2 (VBUS), J5.A4 (VBUS), J5.A9 (VBUS), J5.B4 (VBUS), J5.B9 (VBUS), R1.1, U7.5 (VIN)
GND: C1.2, C2.2, C3.2, C4.2, C5.2, C6.2, C7.2, C8.1, C9.2, D1.3 (-), D2.1, J1.1, J2.1, J3.5 (GND), J3.6 (GND), J5.A1 (GND), J5.A12 (GND), J5.B1 (GND), J5.B12 (GND), J5.S1 (SHIELD), R3.2, R5.2, R6.1, SW1.2, U1.2 (LR), U1.3 (GND), U6.1 (GND), U6.2 (GND), U6.42 (GND), U6.43 (GND), U6.46 (GND), U6.47 (GND), U6.48 (GND), U6.49 (GND), U6.50 (GND), U6.51 (GND), U6.52 (GND), U6.53 (GND), U6.54 (GND), U6.55 (GND), U6.56 (GND), U6.57 (GND), U6.58 (GND), U6.59 (GND), U6.60 (GND), U6.61 (GND), U6.62 (GND), U6.63 (GND), U6.64 (GND), U6.65 (GND), U7.2 (GND), U7.7 (GND)
LED: D2.2, J2.2, U6.8 (GPIO4)
unnamed: J1.2, U6.25 (GPIO21)
unnamed: J5.A5 (CC1), R5.1
unnamed: J5.B5 (CC2), R6.2
unnamed: C9.1, R2.2, U6.45 (EN)
PUSH: SW1.1, U6.10 (GPIO6)
SCK: U1.4 (SCK), U6.38 (GPIO42)
SD: U1.6 (SD), U6.36 (GPIO40)
WS: U1.1 (WS), U6.37 (GPIO41)

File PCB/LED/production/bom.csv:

Designator,Footprint,Quantity,Value,LCSC Part #
C1,CP_EIA-3528-21_Kemet-B,1,220uF Tant,C122649
C10,C_0603_,1,10uF 35V,C194427
C11,C_0603_,1,10uF 6.3V,C1691
C12,C_0603_,1,100nF,
"C2, C4, C8",C_0402,3,100nF,
C3,C_0603,1,22uF,
"C5, C6, C7",C_0603,3,10uF 35V,C194427
C9,C_0402,1,1uF,
D1,SMD1010,1,XL-1010RGBC-WS2812B,C5349953
D3,D_SOD-523,1,5V,C968173
J2,WAGO-2060-453-998-404,1,Wago,C2765056
J5,USB-C-Socket-H,1,USB-C-Socket-H,C709357
L2,L_4x4_,1,10uH,
"R1, R7",R_0402,2,124K,
R14,R_0402_,1,39k2,
R15,R_0402_,1,1M,
"R2, R3",R_0402,2,10K,
R4,R_0402_,1,124k,
"R5, R6",R_0402,2,5K1,
U1,ICS43434_MEMS_Mic,1,ICS43434_MEMS_Mic,C5656610
U6,ESP32-S3-MINI-1,1,ESP32-S3-MINI-1,C3013941
U7,SOT-23-6-MD8942,1,MD8942,C2684786
